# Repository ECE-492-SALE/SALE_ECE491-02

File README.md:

# SALE_ECE491-02
Smart Assistive Living Environment (SALE) Senior Design project at Lafayette College

## Setup

### If you're downloading this on a new device, follow these steps

Open a Developer PowerShell from the Start Menu using the Start->All apps- >Raspberry Pi Pico SDK v1.5.5->Pico – Developer PowerShell I also suggest that you right-click on this menu entry and select “Pin to Start” for faster access in the future.

cd into your Documents folder

Run the following commands:
```bash
mkdir pico
cd pico
git clone -b master https://github.com/raspberrypi/pico-sdk.git
cd pico-sdk 
git submodule update --init 
cd .. 
git clone -b master https://github.com/raspberrypi/pico-examples.git
git clone https://github.com/priskillaw/SALE_ECE491-02.git
```

## Before making any changes, follow these steps

Open a Developer PowerShell 

cd into SALE_ECE491-02

Run "git pull"

You can start working now. Open Pico - Visual Studio Code

## To run things
```bash
cd build 
cmake -G "NMake Makefiles" .. 
nmake
```

Reboot the pico, then drag and drop the .uf2 file from the build file into the pico in file explorer

## To push things
cd into SALE_ECE491-02
```bash
git add Folder_Name
git commit -m "message/notes"
git push
```

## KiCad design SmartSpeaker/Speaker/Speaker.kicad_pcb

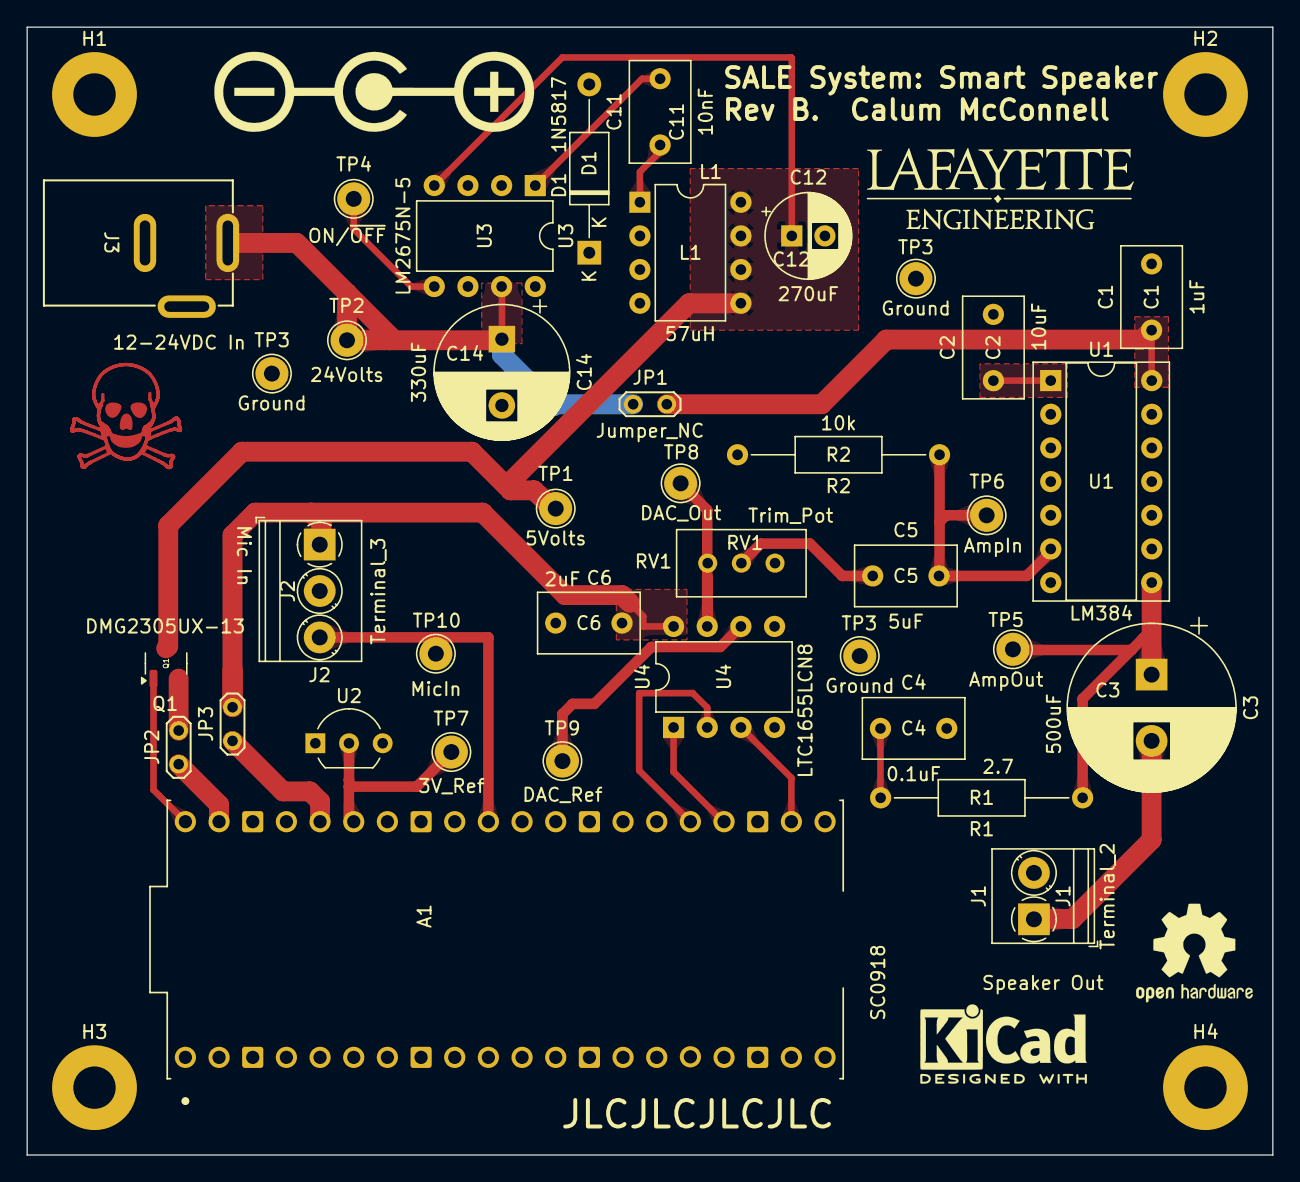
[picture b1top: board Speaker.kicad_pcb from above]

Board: 2 copper layers, 94.0 x 85.1 mm, 42 parts (0 on the bottom side), 25 nets.

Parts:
A1: SC0918; MODULE_SC0918
C1: 1uF; C_Disc_D7.5mm_W4.4mm_P5.00mm
C2: 10uF; C_Disc_D7.5mm_W4.4mm_P5.00mm
C3: 500uF; CP_Radial_D12.5mm_P5.00mm
C4: 0.1uF; C_Disc_D7.5mm_W4.4mm_P5.00mm
C5: 5uF; C_Disc_D7.5mm_W4.4mm_P5.00mm
C6: 2uF; C_Disc_D7.5mm_W4.4mm_P5.00mm
C11: 10nF; C_Disc_D7.5mm_W4.4mm_P5.00mm
C12: 270uF; CP_Radial_D6.3mm_P2.50mm
C14: 330uF; CP_Radial_D10.0mm_P5.00mm
D1: 1N5817; D_A-405_P12.70mm_Horizontal
H1, H2, H3, H4: MountingHole_Pad; MountingHole_3.2mm_M3_Pad
J1: Terminal_2; TerminalBlock_Phoenix_PT-1,5-2-3.5-H_1x02_P3.50mm_Horizontal
J2: Terminal_3; TerminalBlock_Phoenix_PT-1,5-3-3.5-H_1x03_P3.50mm_Horizontal
J3: 54-00166; CONN3_54-00166_TEN
JP1, JP2, JP3: Jumper_NC; TestPoint_2Pads_Pitch2.54mm_Drill0.8mm
L1: 57uH; DIP-8_W7.62mm
Q1: DMG2305UX-13; SOT-23-3
R1: 2.7; R_Axial_DIN0207_L6.3mm_D2.5mm_P15.24mm_Horizontal
R2: 10k; R_Axial_DIN0207_L6.3mm_D2.5mm_P15.24mm_Horizontal
RV1: Trim_Pot; Potentiometer_Bourns_3296W_Vertical
TP1: 5Volts; TestPoint_THTPad_D2.5mm_Drill1.2mm
TP2: 24Volts; TestPoint_THTPad_D2.5mm_Drill1.2mm
TP3, TP3#2, TP3#3: Ground; TestPoint_THTPad_D2.5mm_Drill1.2mm
TP4: ON/~{OFF}; TestPoint_THTPad_D2.5mm_Drill1.2mm
TP5: AmpOut; TestPoint_THTPad_D2.5mm_Drill1.2mm
TP6: AmpIn; TestPoint_THTPad_D2.5mm_Drill1.2mm
TP7: 3V_Ref; TestPoint_THTPad_D2.5mm_Drill1.2mm
TP8: DAC_Out; TestPoint_THTPad_D2.5mm_Drill1.2mm
TP9: DAC_Ref; TestPoint_THTPad_D2.5mm_Drill1.2mm
TP10: MicIn; TestPoint_THTPad_D2.5mm_Drill1.2mm
U1: LM384; DIP-14_W7.62mm_Socket
U2: LM4040LP-3; TO-92_Inline_Wide
U3: LM2675N-5; DIP-8_W7.62mm
U4: LTC1655LCN8; DIP-8_W7.62mm

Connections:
/Adafruit_1713_Microphone/OUTPUT: A1.31 (GP26), J2.3, TP10.1
/AudioOut: C3.1, R1.1, TP5.1, U1.8
/Power_converter/5VOut: C12.1, L1.5, L1.6, L1.7, L1.8, Q1.3 (D), TP1.1, U3.4 (FB)
/Power_converter/VSwitch: C11.1, D1.1 (K), L1.1, L1.2, L1.3, L1.4, U3.8 (VSW)
/Power_converter/VoltageIn: C14.1, J3.1, JP1.1 (A), TP2.1, U3.7 (VIN)
/SpeakerOut: C3.2, J1.1
GND: A1.3 (GND), A1.8 (GND), A1.13 (GND), A1.18 (GND), A1.23 (GND), A1.28 (GND), A1.32 (GP27), A1.33 (AGND), A1.38 (GND), C1.2, C2.2, C4.2, C6.2, C12.2, C14.2, D1.2 (A), H1.1, H2.1, H3.1, H4.1, J1.2, J2.2, J3.3, R2.2, RV1.1, TP3.1, TP3#2.1, TP3#3.1, U1.2 (+), U1.3 (GND), U1.4 (GND), U1.5 (GND), U1.7 (GND), U1.10 (GND), U1.11 (GND), U1.12 (GND), U2.1 (NC), U2.3 (A), U3.6 (GND), U4.5 (GND)
unnamed: A1.36 (3V3_OUT), JP3.1 (A)
unnamed: A1.35 (ADC_VREF), TP7.1, U2.2 (K)
unnamed: A1.22 (GP17), U4.3 (~CS/LD)
unnamed: A1.24 (GP18), U4.1 (CLK)
unnamed: A1.25 (GP19), U4.2 (DIN)
unnamed: A1.40 (VBUS), Q1.1 (G)
unnamed: A1.39 (VSYS), JP2.1 (A)
unnamed: C4.1, R1.2
unnamed: C5.1, RV1.2
unnamed: C1.1, JP1.2 (B), U1.14 (VS)
unnamed: JP2.2 (B), Q1.2 (S)
unnamed: C5.2, R2.1, TP6.1, U1.6 (-)
unnamed: C2.1, U1.1 (BYPASS)
unnamed: C11.2, U3.1 (CB)
unnamed: TP4.1, U3.5 (ON/~OFF)
unnamed: TP9.1, U4.6 (REF)
unnamed: RV1.3, TP8.1, U4.7 (VOUT)
VDD: C6.1, J2.1, JP3.2 (B), U4.8 (VCC)

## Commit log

2025-02-07 Copied over from picow-iot
2025-02-10 Bring in new example project: https://github.com/daniloc/PicoW_HomeAssistant_Starter/tree/main at commit fa77414
2025-02-10 manually set IP address
2025-02-10 add some other files (priscilla forgot to commit) -- calum
2025-02-11 add reference to existing calum repository
2025-02-11 update new submodule with my latest changes
2025-02-11 Fix .gitmodules
2025-02-12 Added credit and other notes
2025-04-11 Fix broken git repos --calum
2025-04-23 Changes to get pillbox to work (after re-fixing broken git repos) --calum
2025-04-23 bring in smart light as starting point for smart pillbox
2025-04-23 Working Smart Door as basic switch :) - Chris
2025-04-24 Bring in link to Scott's work
2025-04-24 Add ESPHome device configs to macrorepo
2025-04-27 rough out an alternate method to do the relay
2025-04-27 improvements
2025-04-28 Update CalumTestRelay.py
    Works with curl test
2025-04-28 Update CalumTestRelay.py
    Home Assistant is now able to control Roku, no timeout errors.
2025-04-28 Update CalumTestRelay.py
    Update commit before logging out
2025-05-05 Update CalumTestRelay.py
    Misc changes during testing
2025-05-05 write some nonblocking code
2025-05-05 Tweaks for the relay in testing-- it works!
    Able to play sound via home assistant
    Music assistant isn't working yet (internet says it might never)
2025-05-05 update submodules
2025-05-05 Switched pin for protoboard, changed to button - Chris
2025-05-08 Fixed names - Chris
2025-05-08 Changed display name -Chris
2025-05-18 Create Temp
2025-05-19 Update CalumTestRelay.py
    Added garbage collection to avoid "no memory" errors
2025-05-19 Raise SmartSpeaker to proper folder
2025-05-19 reorganized and added 3d print files
2025-05-19 Add unique configurations and automations
2025-05-19 Add SMD_05_19.aia to Smart Mobile Device
2025-05-19 Modified main.py to make Smart TV easier to adapt
2025-05-19 Update README.md for Smart TV
2025-05-19 Create t
2025-05-19 add schematics
2025-05-19 Add smart speaker code
2025-05-19 Create filler
2025-05-19 add lastest speaker case designs
2025-05-19 clear out gitmodules for this new organization
2025-05-19 add bom, resolve issue with gitignore
2025-05-19 Update and rename temp to readme
